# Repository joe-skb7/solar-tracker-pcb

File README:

Solar tracker PCB
-----------------

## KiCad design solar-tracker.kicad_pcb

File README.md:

# Solar tracker PCB

This project contains solar tracker PCB I made for my dad's project.

3D Model, Front View:

3D Model, Bottom View:

Schematic:

I used KiCAD 4.0.7 for this PCB, but it should open fine in different versions,
as I keep `-cache.lib` file in this repo.

Original schematic can be found in `doc/scheme.jpg`. Things that I changed:
* properly terminated unused OPAMP parts
* added limit switches connection

## Schematic explanation

LDR1 and LDR2 photo-resistors yield signal which is used to determine in which
direction PV unit (solar panel) should be rotated, i.e. in which direction
we have more light radiation.

Signal from photo-resistors is being compared further by comparators built on
U1A and U1B OPAMPs. Reference voltage level is generated by dividers built on
R1, R2 resistors and RV1, RV2 trim-pots.

RV1 trim-pot is used to adjust this reference voltage point, so that motor
stands still when both photo-resistors are receiving the same light level.
RV2 is used to setup hysteresis level, so that motor is not moving when the
light difference on photo-resistors is small.

H-bridge formed by Q1-Q4 transistors is powering the motor, according to control
signals from comparators. Transistors are working in switch mode, as comparators
yield only 0 or VCC:

    V_out = 0,   if V+ < V-
    V_out = Vcc, if V+ > V-

D1-D4 are just flyback diodes, providing the path for back EMF discharge from
motor's coil, preventing other elements from it (transistors can be burnt, or
limit switches can be carbonized due to arcing).

C1 provides some of the energy required by the motor during the initial spike of
each turn-on.

**TODO**: Add C2 (10u x 50V) close to C1

**TODO**: Add 100n capacitor close to U1 chip (required by datasheet)

R3 and R4 are used to properly terminate unused OPAMPs (U1C, U1D).

J5 and J6 terminal blocks (along with D5, D6 diodes) are used for connecting the
limit switches.

### Power consideration

Power voltage: 9V must be used. It's because the motor will receive only
`Vcc - 2.6` Volts, due to voltage drop across transistors and also on OPAMP,
as it's not Rail-to-Rail one. MG995 requires the voltage to be 4.8V ... 7.2V,
so the voltage drop must be accounted for.

Power current: 2A or more. Because MG995 can consume up to 1.5A on start
("stall current").

In case when 12V battery is used (it's common in solar panels appliance),
I suggest one to use external 12V-to-9V buck converter (2A rated, or more). It's
efficient (95%), small enough, and usually costs only $2-$3. No need to
over-complicate tracker schematic by adding voltage regulator scheme to it.

### Limit switches

`doc/limit-switch/` directory contains two possible schemes to implement limit
switches in H-bridge, with pros/cons overview. I personally like the second
scheme the best, so I implemented it in this project.

### EMI note

Notice that switching of DC motor's brushes leads to EMI, which may affect your
external circuits (especially digital ones, like MCUs). In that case you should
install EMI suppressor on your motor leads.

## Prepared files

`out/` directory contains ready to use files for manufacturing the PCB.

### Toner Transfer Method

See `out/toner-transfer-method/` for ready to use files.

Notes:
1. Remove the copper pour from both sides of PCB
2. Notice the Vias and front layer tracks. You need to solder jumper wires
   instead of them, in case if you are using single sided copper clad board.

### Manufacturing at plant

You can order the PCB to be manufactured on plant, e.g. at Seeed Studio (Fusion
PCB) or JLCPCB. Gerber files and drill file are prepared at `out/gerber/`.

## References

### Original scheme description and discussion

[1] http://www.electroschematics.com/8019/diy-solar-tracker-system/

[2] http://izobreteniya.net/solnechnyiy-treker-svoimi-rukami/

[3] http://radiokot.ru/forum/viewtopic.php?f=3&t=144321

[4] https://www.youtube.com/watch?v=UQyiuxo1Wvo

### Unused OPAMPs: proper termination

[5] https://www.electronicproducts.com/Analog_Mixed_Signal_ICs/Amplifiers/Properly_terminating_an_unused_op_amp.aspx

### EMI suppressor

[6] http://reprap.org/wiki/GM3_Noise_Suppressor_v1.0

## Authors

**Sam Protsenko**

## License

This project is licensed under the GPLv3.

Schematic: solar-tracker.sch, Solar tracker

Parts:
C1: 100n; C_Disc_D5.0mm_W2.5mm_P5.00mm
D1, D2, D3, D4: 1N5402; D_DO-201AD_P15.24mm_Horizontal
D5, D6: 1N5402; D_DO-201AD_P5.08mm_Vertical_KathodeUp
J1: LDR1; JST_XH_B02B-XH-A_1x02_P2.50mm_Vertical
J2: LDR2; JST_XH_B02B-XH-A_1x02_P2.50mm_Vertical
J3: Motor; TerminalBlock_Phoenix_MKDS-1,5-2_1x02_P5.00mm_Horizontal
J4: Power_9V; TerminalBlock_Phoenix_MKDS-1,5-2_1x02_P5.00mm_Horizontal
J5: FWD_Limit; TerminalBlock_Phoenix_MKDS-1,5-2_1x02_P5.00mm_Horizontal
J6: REV_Limit; TerminalBlock_Phoenix_MKDS-1,5-2_1x02_P5.00mm_Horizontal
MK1, MK2, MK3, MK4: Mounting_Hole_PAD; MountingHole_3.2mm_M3_Pad
Q1, Q2: TIP41C; TO-220-3_Vertical
Q3, Q4: TIP42C; TO-220-3_Vertical
R1: 15k; R_Axial_DIN0207_L6.3mm_D2.5mm_P10.16mm_Horizontal
R2: 47k; R_Axial_DIN0207_L6.3mm_D2.5mm_P10.16mm_Horizontal
R3, R4: 470k; R_Axial_DIN0207_L6.3mm_D2.5mm_P10.16mm_Horizontal
R10, R11: 0R; R_Axial_DIN0207_L6.3mm_D2.5mm_P10.16mm_Horizontal
RV1: 100k; Potentiometer_Bourns_3266W_Vertical
RV2: 10k; Potentiometer_Bourns_3266W_Vertical
U1: LM324; DIP-14_W7.62mm

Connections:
+9V: C1.1, D1.1 (K), D2.1 (K), J1.2, J4.2, Q1.2 (C), Q2.2 (C), R3.1, RV1.1, RV1.2, U1.4 (V+)
GND: C1.2, D3.2 (A), D4.2 (A), J2.1, J4.1, MK1.1, MK2.1, MK3.1, MK4.1, Q3.2 (C), Q4.2 (C), R2.2, R4.2, U1.11 (V-)
unnamed: D1.2 (A), D3.1 (K), D5.2 (A), J3.1, J5.2
unnamed: D2.2 (A), D4.1 (K), D6.2 (A), J3.2, J6.1
unnamed: D5.1 (K), J5.1, Q1.3 (E), Q3.3 (E)
unnamed: D6.1 (K), J6.2, Q2.3 (E), Q4.3 (E)
unnamed: J1.1, J2.2, U1.3 (+), U1.6 (-)
unnamed: Q1.1 (B), Q3.1 (B), R10.1
unnamed: Q2.1 (B), Q4.1 (B), R11.1
unnamed: R1.1, RV1.3
unnamed: R1.2, RV2.1, RV2.2, U1.2 (-)
unnamed: R2.1, RV2.3, U1.5 (+)
unnamed: R3.2, R4.1, U1.10 (+), U1.12 (+)
unnamed: R10.2, U1.1
unnamed: R11.2, U1.7
unnamed: U1.8, U1.9 (-)
unnamed: U1.13 (-), U1.14

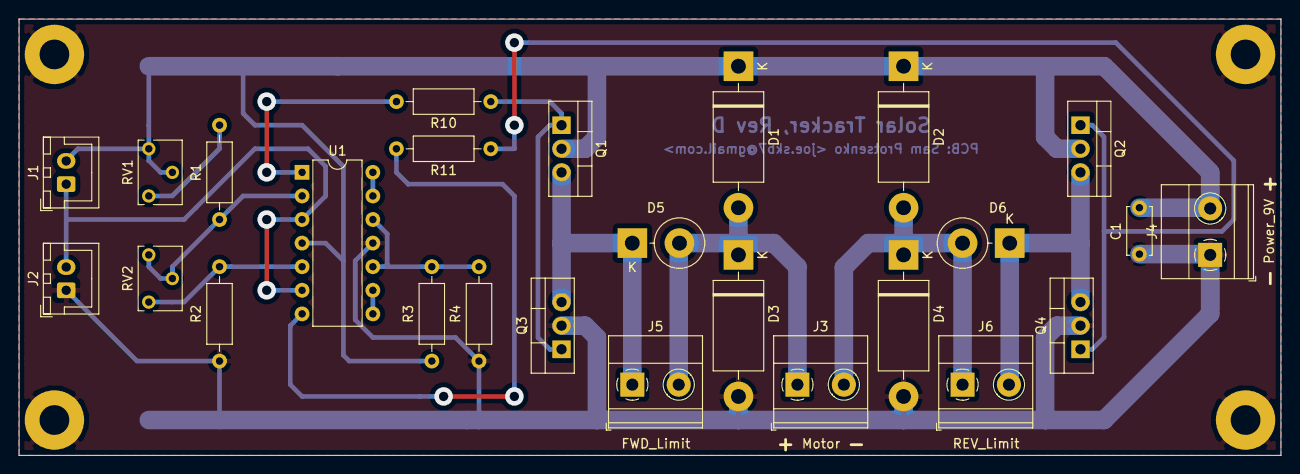
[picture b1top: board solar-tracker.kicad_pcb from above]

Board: 2 copper layers, 135.9 x 47.0 mm, 30 parts (0 on the bottom side), 17 nets.

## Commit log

2017-11-25 Add README file
2017-11-25 Add initial KiCAD files
2017-11-26 Add .gitignore file
2017-11-26 Started routing the PCB layout
2017-11-26 doc: Add links
2017-11-26 doc: Add original schematic
2017-11-26 Add cache lib
    -cache.lib: a local copy of all the symbols used in the corresponding
    schematic, so that when the folder containing a KiCad project is copied
    to a different PC, the schematic can still be opened and printed and
    will still look the same as the original draughtsperson intended - even
    if that other PC does not have those symbols in its main libraries
    (or has symbols that coincidentally have the same name but are
2017-11-27 Create PCB layout for blocks
2017-11-27 Finish PCB
2017-11-27 pcb: Add PCB edges and copper pour
2017-11-27 pcb: Reduce via size
2017-11-27 schematic: Move unused OPAMP block to the right
2017-11-27 pcb: Remove copper pour
    Prepare PCB for LUT (toner transfer method).
2017-11-27 README: Improve README file
2017-11-27 schematic: Move C1 closer to H-bridge
    Where it belongs to.
2017-11-27 pcb: Bring C1 close to H-bridge
2017-11-27 README: Add D1-D4 and C1 description
2017-11-28 TODO: Add TODO list
2017-11-29 doc: Add limit switches schemes and description
2017-11-29 doc: Update limit switches schematic #2
    Move flyback diodes close to the motor, where they belong. While at it,
    add +/- labels on the motor and update the description.
2017-11-29 README: Update README file
2017-11-29 TODO: Update TODO list
2017-12-02 Update schematic and PCB to Revision B
    - Add limit switches + diodes
    - Vcc -> 9V
    - Use JST XH connectors for photo-resistors (instead of screw terminal
    blocks)
    - Add mounting holes to schematic
    - Bring back the copper pour; for Toner Transfer Method one can simply
2017-12-02 doc: Add screenshots
    And show them in README.md.
2017-12-02 out: Add ready to use files for manufacturing
    Also update README file, while at it.
2017-12-02 netlist: Remove Netlist file
    It contains absolute path from my machine. If needed, it can be easily
    generated on user's machine from Eeschema.
2017-12-02 README: Add power consideration section
2017-12-02 README: Add limit switches note
2017-12-02 README: Move links to README file
2017-12-08 README: Add schematic screenshot
2018-04-07 Remove electrolytic capacitor
    It's slowing really slow, preventing to measure final voltage on unused
    OPAMPs terminals.
2018-04-07 Move old RevB files to corresponding directories
2018-04-07 README: Fix README w.r.t. new RevC
2018-05-13 schematic: Add means to separate control/power parts
    Add 0-Ohm R10, R11 so that user is able to separate control board from
    power board for debugging purposes.
2018-05-13 pcb: Route PCB after adding R10, R11
    Route new circuit correspondingly.
2018-05-13 Update out/ and doc/
    Update all output files to Rev D.
2018-05-13 README: Update images links
2018-05-13 pcb: Add missing layers
    B.Mask and B.SilkS layers were missing by default. But they are needed
    for manufacturing (corresponding Gerber files must be generated). Enable
    those layers in:
    Design Rules -> Layers Setup
    and re-generate Gerber files.
    While at it, move terminal values to silk layer, which can be convenient
2018-10-22 README: Add TODO comments
2019-01-03 Migrate to KiCad 5.0
2025-08-15 Create LICENSE
